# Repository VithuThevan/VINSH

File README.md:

# VINSH
This is just a rough idea of our new innovation of "Smart Fan cleaning system"

The repository consists of codes, proteus simulations and pcb designs (Both Complete and Individual)

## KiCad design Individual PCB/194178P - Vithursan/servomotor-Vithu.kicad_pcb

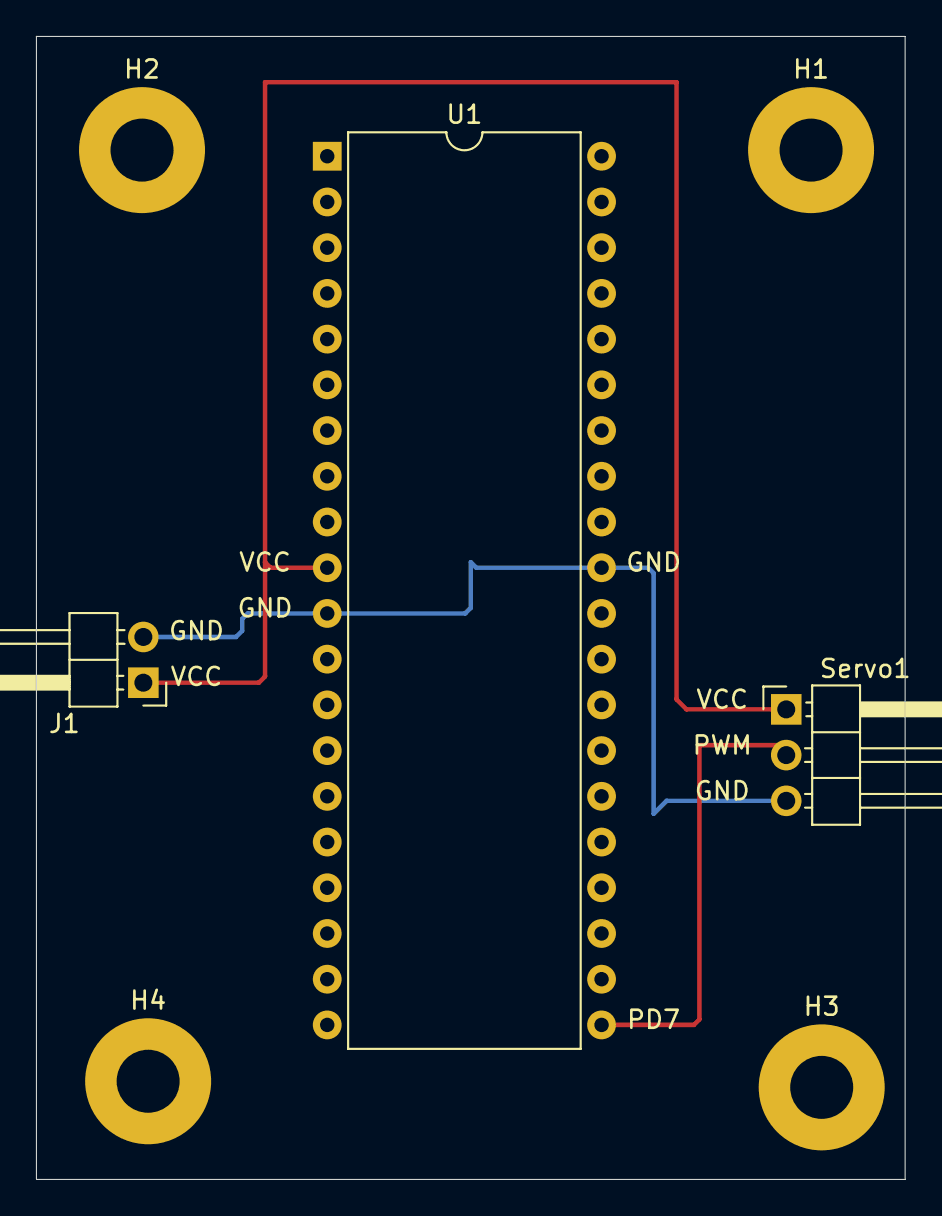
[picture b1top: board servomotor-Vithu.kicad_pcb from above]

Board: 2 copper layers, 48.3 x 63.5 mm, 7 parts (0 on the bottom side), 3 nets.

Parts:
H1, H2, H3, H4: MountingHole; MountingHole_3.5mm_Pad
J1: Conn_01x02; PinHeader_1x02_P2.54mm_Horizontal
Servo1: Conn_01x03; PinHeader_1x03_P2.54mm_Horizontal
U1: ATmega32-16PU; DIP-40_W15.24mm

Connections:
+5V: J1.1, Servo1.1, U1.10
GND: J1.2, Servo1.3, U1.11, U1.31
unnamed: Servo1.2, U1.21

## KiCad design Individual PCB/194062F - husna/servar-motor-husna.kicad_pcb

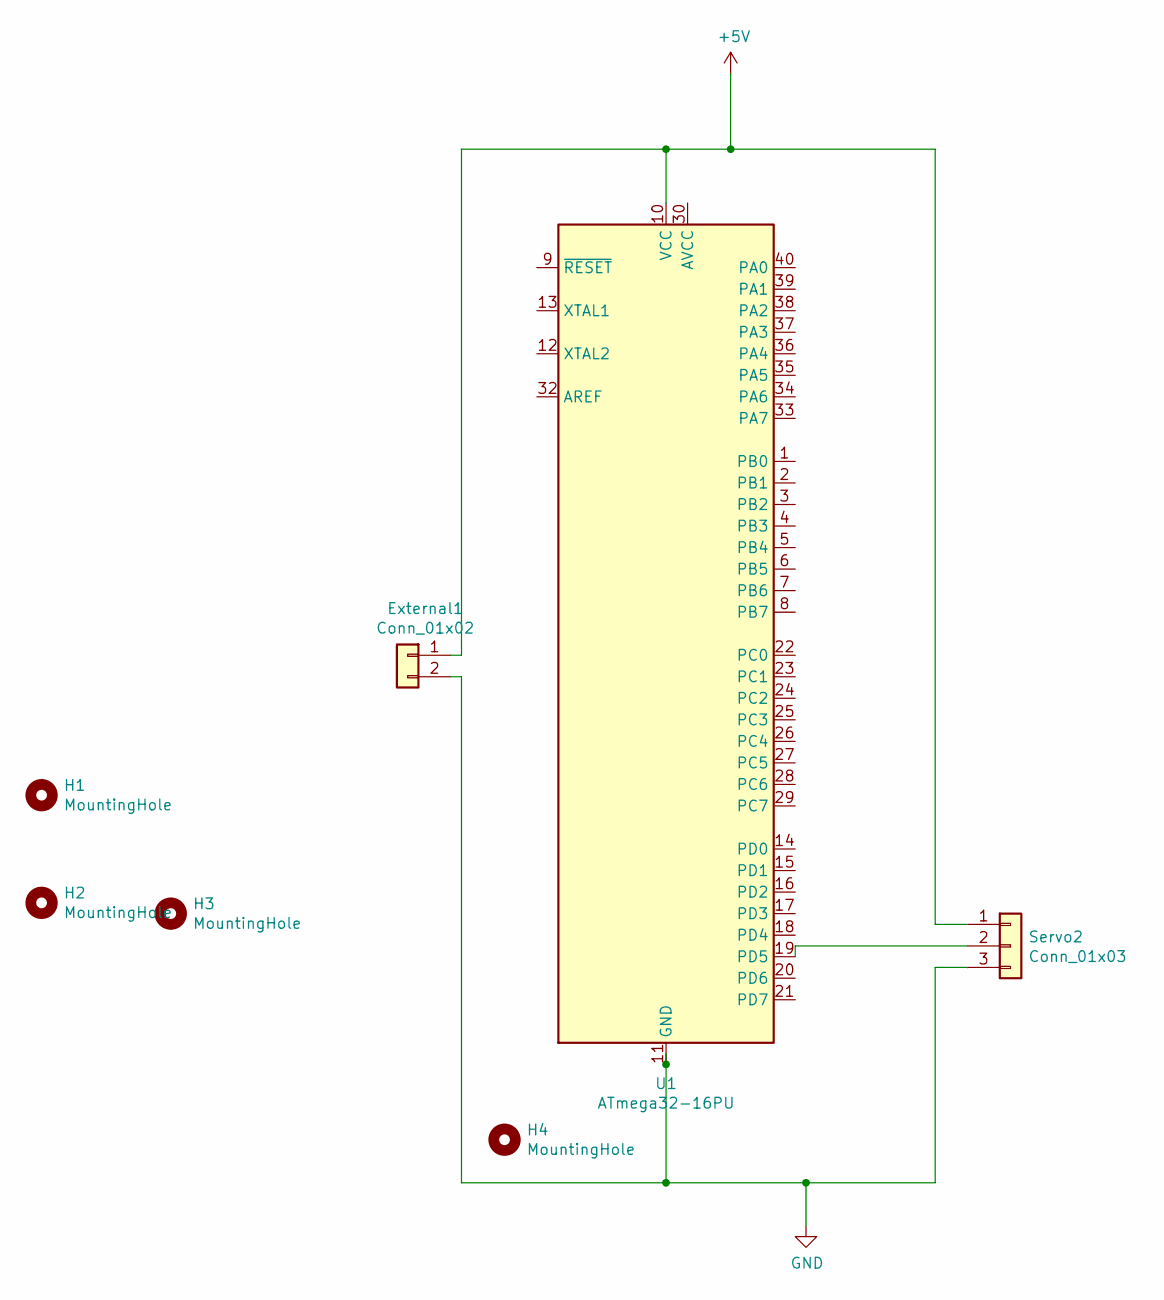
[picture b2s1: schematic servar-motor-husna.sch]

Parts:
External1: Conn_01x02; PinHeader_1x02_P2.54mm_Horizontal
H1, H2, H3, H4: MountingHole; MountingHole_3.5mm_Pad
Servo2: Conn_01x03; PinHeader_1x03_P2.54mm_Horizontal
U1: ATmega32-16PU; DIP-40_W15.24mm

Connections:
+5V: External1.1, Servo2.1, U1.10 (VCC)
GND: External1.2, Servo2.3, U1.11 (GND), U1.31 (GND)
unnamed: Servo2.2, U1.19 (PD5)

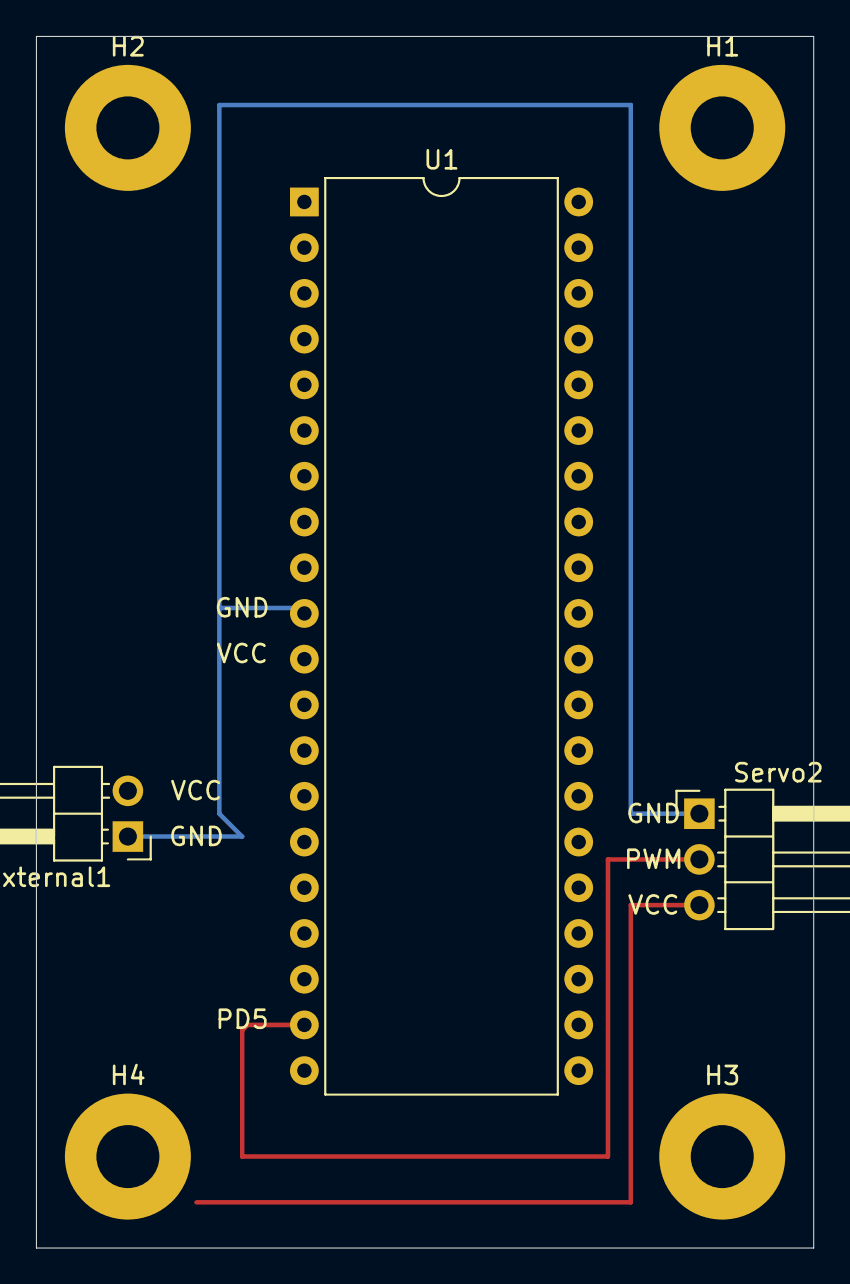
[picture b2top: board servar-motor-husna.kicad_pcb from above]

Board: 2 copper layers, 43.2 x 67.3 mm, 7 parts (0 on the bottom side), 3 nets.

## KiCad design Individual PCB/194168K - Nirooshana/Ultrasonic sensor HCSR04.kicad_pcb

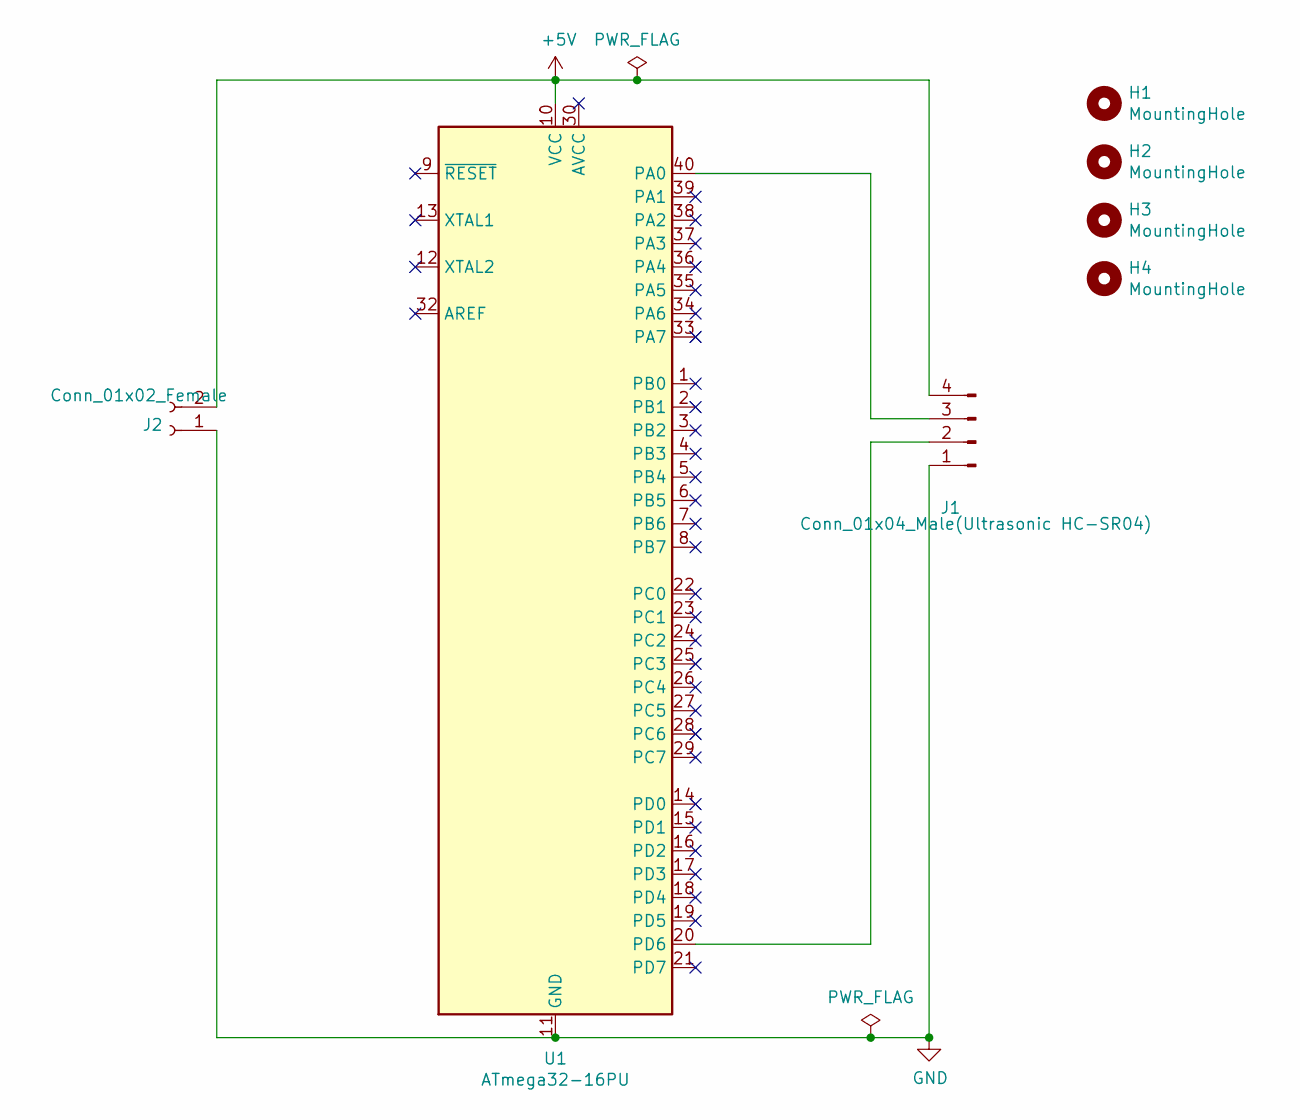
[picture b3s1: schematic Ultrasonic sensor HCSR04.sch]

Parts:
H1, H2, H3, H4: MountingHole; MountingHole_2.5mm_Pad
J1: Conn_01x04_Male(Ultrasonic HC-SR04); PinHeader_1x04_P2.54mm_Vertical
J2: Conn_01x02_Female; PinHeader_1x02_P2.54mm_Vertical
U1: ATmega32-16PU; DIP-40_W15.24mm

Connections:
+5V: J1.4, J2.2, U1.10 (VCC)
GND: J1.1, J2.1, U1.11 (GND), U1.31 (GND)
unnamed: J1.2, U1.20 (PD6)
unnamed: J1.3, U1.40 (PA0)

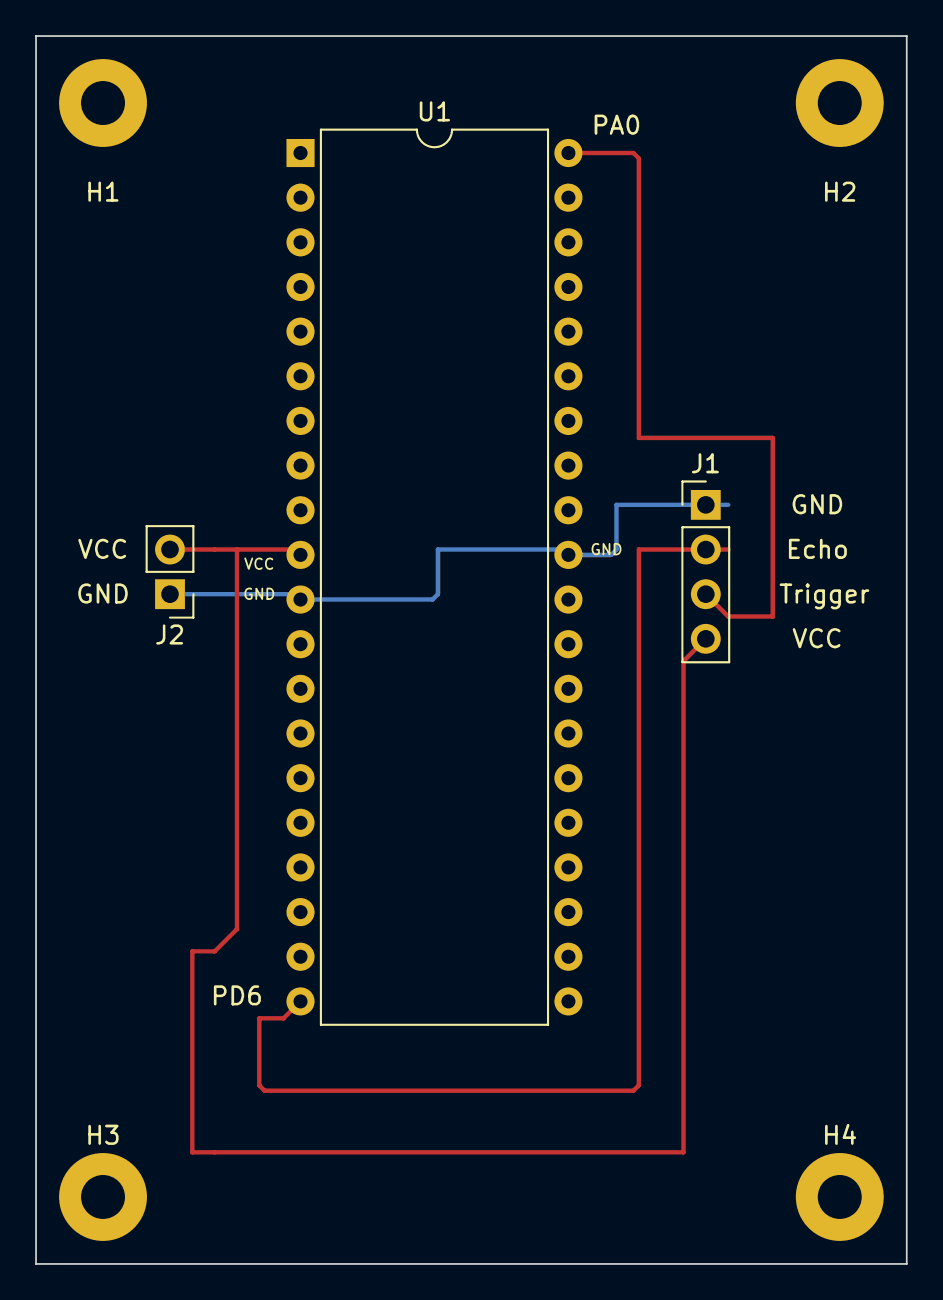
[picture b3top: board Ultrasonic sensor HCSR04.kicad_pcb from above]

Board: 2 copper layers, 49.5 x 69.8 mm, 7 parts (0 on the bottom side), 4 nets.

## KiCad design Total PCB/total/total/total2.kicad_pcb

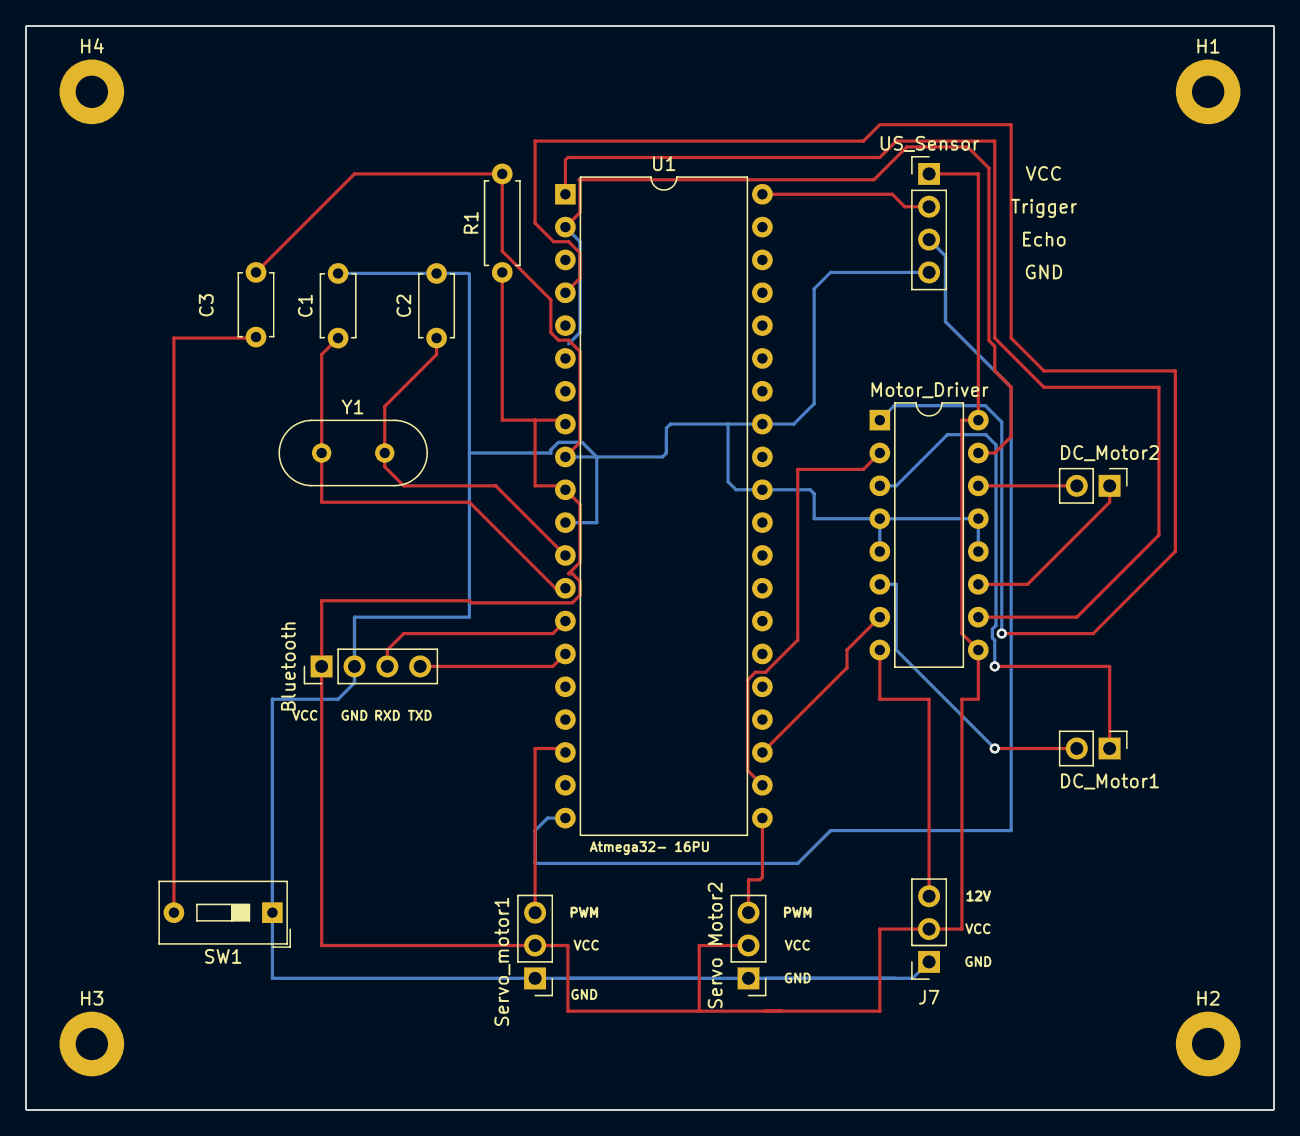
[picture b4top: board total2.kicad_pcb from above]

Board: 2 copper layers, 96.5 x 83.8 mm, 19 parts (0 on the bottom side), 22 nets.

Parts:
Bluetooth: Conn_01x04_Male; PinHeader_1x04_P2.54mm_Vertical
C1, C2, C3: C; C_Disc_D4.7mm_W2.5mm_P5.00mm
DC_Motor1, DC_Motor2: Conn_01x02_Male; PinHeader_1x02_P2.54mm_Vertical
H1, H2, H3, H4: MountingHole; MountingHole_2.5mm_Pad
J7: Conn_01x03_Female; PinSocket_1x03_P2.54mm_Vertical
Motor_Driver: L293D; DIP-16_W7.62mm
R1: R; R_Axial_DIN0207_L6.3mm_D2.5mm_P7.62mm_Horizontal
SW1: SW_SPST; SW_DIP_SPSTx01_Slide_9.78x4.72mm_W7.62mm_P2.54mm
Servo Motor2: Conn_01x03_Male; PinHeader_1x03_P2.54mm_Vertical
Servo_motor1: Conn_01x03_Male; PinHeader_1x03_P2.54mm_Vertical
U1: ATmega32-16PU; DIP-40_W15.24mm
US_Sensor: Conn_01x04_Male; PinHeader_1x04_P2.54mm_Vertical
Y1: Crystal; Crystal_HC49-4H_Vertical

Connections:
+5V: Bluetooth.1, J7.2, Motor_Driver.9, Motor_Driver.16, R1.1, Servo Motor2.2, Servo_motor1.2, U1.10, US_Sensor.1
GND: Bluetooth.2, C1.2, C2.2, J7.1, Motor_Driver.4, Motor_Driver.5, Motor_Driver.12, Motor_Driver.13, SW1.1, Servo Motor2.1, Servo_motor1.1, U1.11, U1.31, US_Sensor.4
unnamed: C1.1, U1.13, Y1.1
unnamed: C2.1, U1.12, Y1.2
unnamed: C3.1, R1.2, U1.9
unnamed: C3.2, SW1.2
unnamed: DC_Motor1.1, Motor_Driver.3
unnamed: DC_Motor1.2, Motor_Driver.6
unnamed: DC_Motor2.1, Motor_Driver.11
unnamed: DC_Motor2.2, Motor_Driver.14
unnamed: U1.40, US_Sensor.2
unnamed: U1.20, US_Sensor.3
unnamed: Servo_motor1.3, U1.18
unnamed: Bluetooth.3, U1.14
unnamed: Bluetooth.4, U1.15
unnamed: Servo Motor2.3, U1.21
unnamed: J7.3, Motor_Driver.8
unnamed: Motor_Driver.10, U1.1
unnamed: Motor_Driver.15, U1.2
unnamed: Motor_Driver.1, U1.4
unnamed: Motor_Driver.2, U1.22
unnamed: Motor_Driver.7, U1.23

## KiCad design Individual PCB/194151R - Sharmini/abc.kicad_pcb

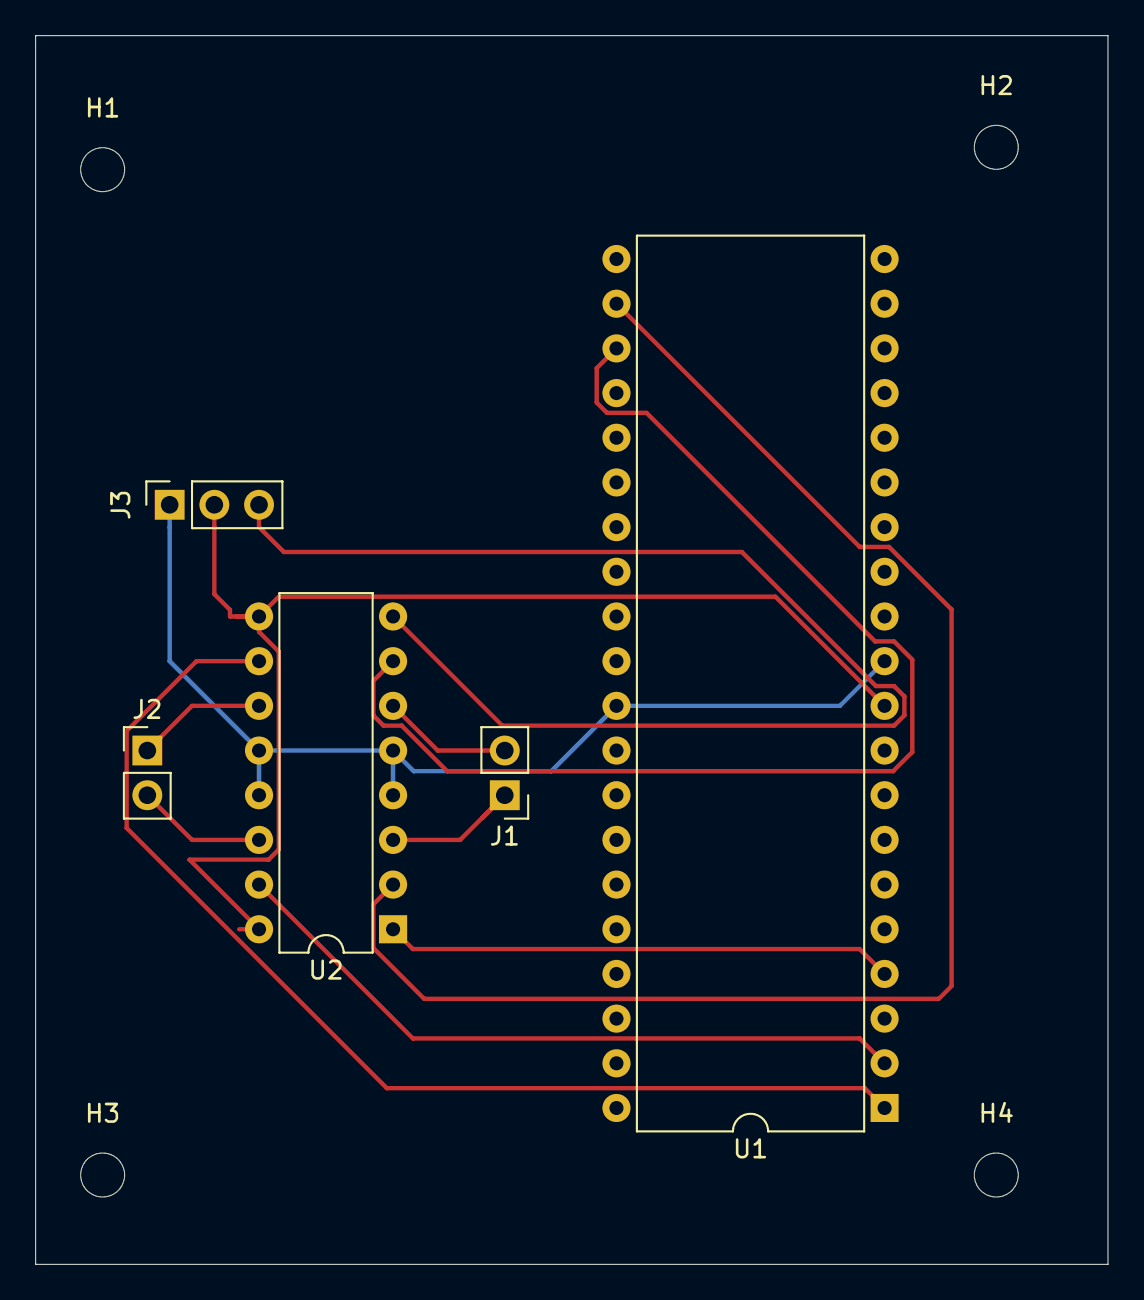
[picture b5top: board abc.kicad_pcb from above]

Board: 2 copper layers, 61.0 x 69.8 mm, 9 parts (0 on the bottom side), 12 nets.

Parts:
H1, H2, H3, H4: MountingHole; MountingHole_2.5mm
J1, J2: Conn_01x02_Male; PinHeader_1x02_P2.54mm_Vertical
J3: Conn_01x03_Female; PinSocket_1x03_P2.54mm_Vertical
U1: ATmega32-16PU; DIP-40_W15.24mm
U2: L293D; DIP-16_W7.62mm

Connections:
unnamed: J1.1, U2.3
unnamed: J1.2, U2.6
unnamed: J2.1, U2.11
unnamed: J2.2, U2.14
unnamed: J3.1, U1.11, U1.31, U2.4, U2.5, U2.12, U2.13
unnamed: J3.2, U1.10, U2.9, U2.16
unnamed: J3.3, U2.8
unnamed: U1.1, U2.10
unnamed: U1.2, U2.15
unnamed: U1.4, U2.1
unnamed: U1.22, U2.2
unnamed: U1.23, U2.7
